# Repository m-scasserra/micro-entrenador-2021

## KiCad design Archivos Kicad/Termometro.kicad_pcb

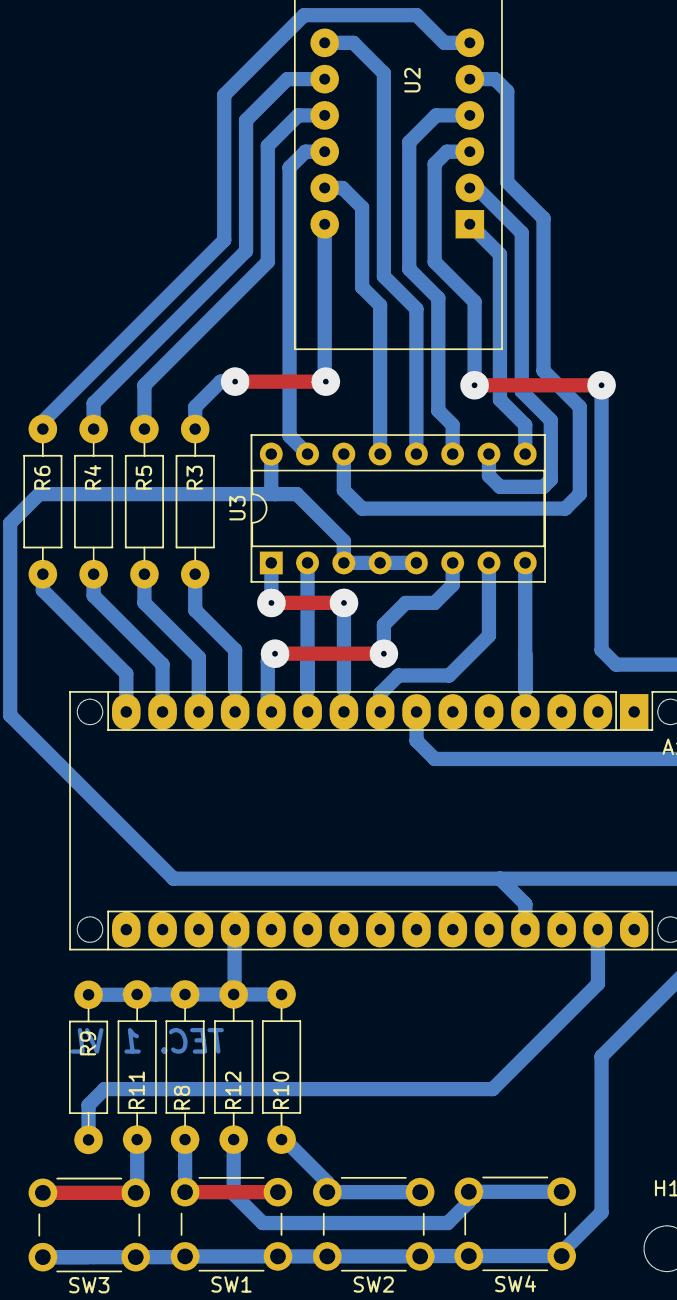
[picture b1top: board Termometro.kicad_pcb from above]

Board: 2 copper layers, 18 parts (0 on the bottom side), 27 nets.

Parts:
A1: Arduino_Nano_v3.x; Arduino_Nano_WithMountingHoles
H1, H2: MountingHole; MountingHole_3.2mm_M3
R3, R4, R5, R6: 470; R_Axial_DIN0207_L6.3mm_D2.5mm_P10.16mm_Horizontal
R8, R9: 1000; R_Axial_DIN0207_L6.3mm_D2.5mm_P10.16mm_Horizontal
R10: 2200; R_Axial_DIN0207_L6.3mm_D2.5mm_P10.16mm_Horizontal
R11: 3300; R_Axial_DIN0207_L6.3mm_D2.5mm_P10.16mm_Horizontal
R12: 4700; R_Axial_DIN0207_L6.3mm_D2.5mm_P10.16mm_Horizontal
SW1, SW2, SW3, SW4: SW_Push; SW_PUSH_6mm_h5mm
U2: CC56-12EWA; CL3641BB
U3: 74LS47; DIP-16_W7.62mm_Socket

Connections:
+5V: A1.27 (+5V), SW1.1, SW2.1, SW3.1, SW4.1, U3.3 (LT), U3.4 (BI), U3.5 (RBI), U3.16 (VCC)
/A: A1.8 (D5), U3.7 (A)
/A0: A1.19 (A0), R8.1, R9.2, R10.1, R11.1, R12.1
/B: A1.9 (D6), U3.1 (B)
/C: A1.10 (D7), U3.2 (C)
/CC1: A1.12 (D9), R3.1
/CC2: A1.13 (D10), R5.1
/CC3: A1.14 (D11), R4.1
/CC4: A1.15 (D12), R6.1
/D: A1.11 (D8), U3.6 (D)
/DPX: A1.7 (D4), U2.3
/a: U2.11, U3.13 (a)
/b: U2.7, U3.12 (b)
/c: U2.4, U3.11 (c)
/d: U2.2, U3.10 (d)
/e: U2.1, U3.9 (e)
/f: U2.10, U3.15 (f)
/g: U2.5, U3.14 (g)
GND: A1.4 (GND), A1.29 (GND), R9.1, U3.8 (GND)
unnamed: R3.2, U2.12
unnamed: R4.2, U2.8
unnamed: R5.2, U2.9
unnamed: R6.2, U2.6
unnamed: R8.2, SW1.2
unnamed: R10.2, SW2.2
unnamed: R11.2, SW3.2
unnamed: R12.2, SW4.2

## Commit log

2022-03-08 Minientrenador con deco BCD a 7 seg
